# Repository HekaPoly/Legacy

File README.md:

# Legacy

Voici le _repository_ pour tous les fichiers du passé obscur de Métis. Amusez-vous à fouiller au travers ;)

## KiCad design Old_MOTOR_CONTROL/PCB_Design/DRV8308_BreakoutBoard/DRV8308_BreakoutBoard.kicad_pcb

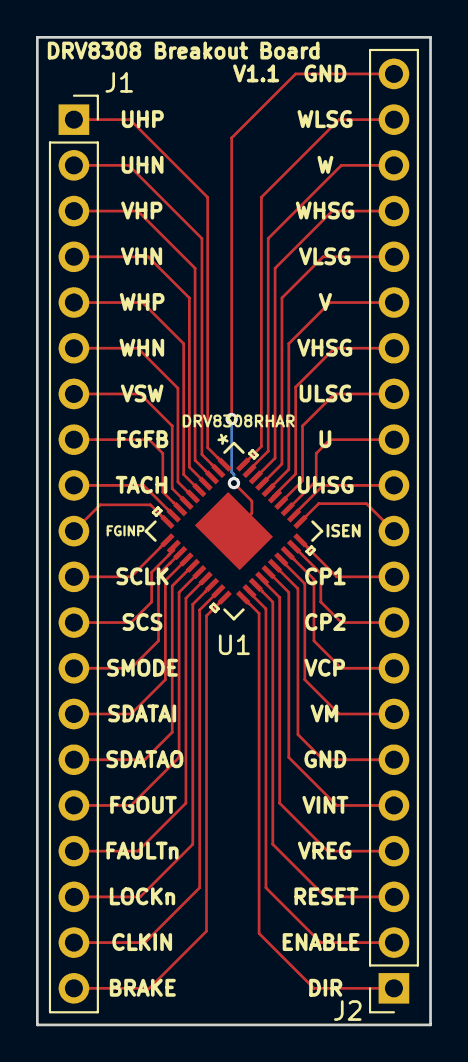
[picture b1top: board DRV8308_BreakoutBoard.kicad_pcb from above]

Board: 2 copper layers, 21.8 x 54.9 mm, 3 parts (0 on the bottom side), 41 nets.

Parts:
J1: Conn_01x20_Female; PinSocket_1x20_P2.54mm_Vertical
J2: Conn_01x21_Female; PinSocket_1x21_P2.54mm_Vertical
U1: DRV8308RHAR

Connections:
unnamed: J1.1, U1.1
unnamed: J1.2, U1.2
unnamed: J1.3, U1.3
unnamed: J1.4, U1.4
unnamed: J1.5, U1.5
unnamed: J1.6, U1.6
unnamed: J1.7, U1.7
unnamed: J1.8, U1.8
unnamed: J1.9, U1.9
unnamed: J1.10, U1.10
unnamed: J1.11, U1.11
unnamed: J1.12, U1.12
unnamed: J1.13, U1.13
unnamed: J1.14, U1.14
unnamed: J1.15, U1.15
unnamed: J1.16, U1.16
unnamed: J1.17, U1.17
unnamed: J1.18, U1.18
unnamed: J1.19, U1.19
unnamed: J1.20, U1.20
unnamed: J2.1, U1.21
unnamed: J2.2, U1.22
unnamed: J2.3, U1.23
unnamed: J2.4, U1.24
unnamed: J2.5, U1.25
unnamed: J2.6, U1.26
unnamed: J2.7, U1.27
unnamed: J2.8, U1.28
unnamed: J2.9, U1.29
unnamed: J2.10, U1.30
unnamed: J2.11, U1.31
unnamed: J2.12, U1.32
unnamed: J2.13, U1.33
unnamed: J2.14, U1.34
unnamed: J2.15, U1.35
unnamed: J2.16, U1.36
unnamed: J2.17, U1.37
unnamed: J2.18, U1.38
unnamed: J2.19, U1.39
unnamed: J2.20, U1.40
unnamed: J2.21, U1.41

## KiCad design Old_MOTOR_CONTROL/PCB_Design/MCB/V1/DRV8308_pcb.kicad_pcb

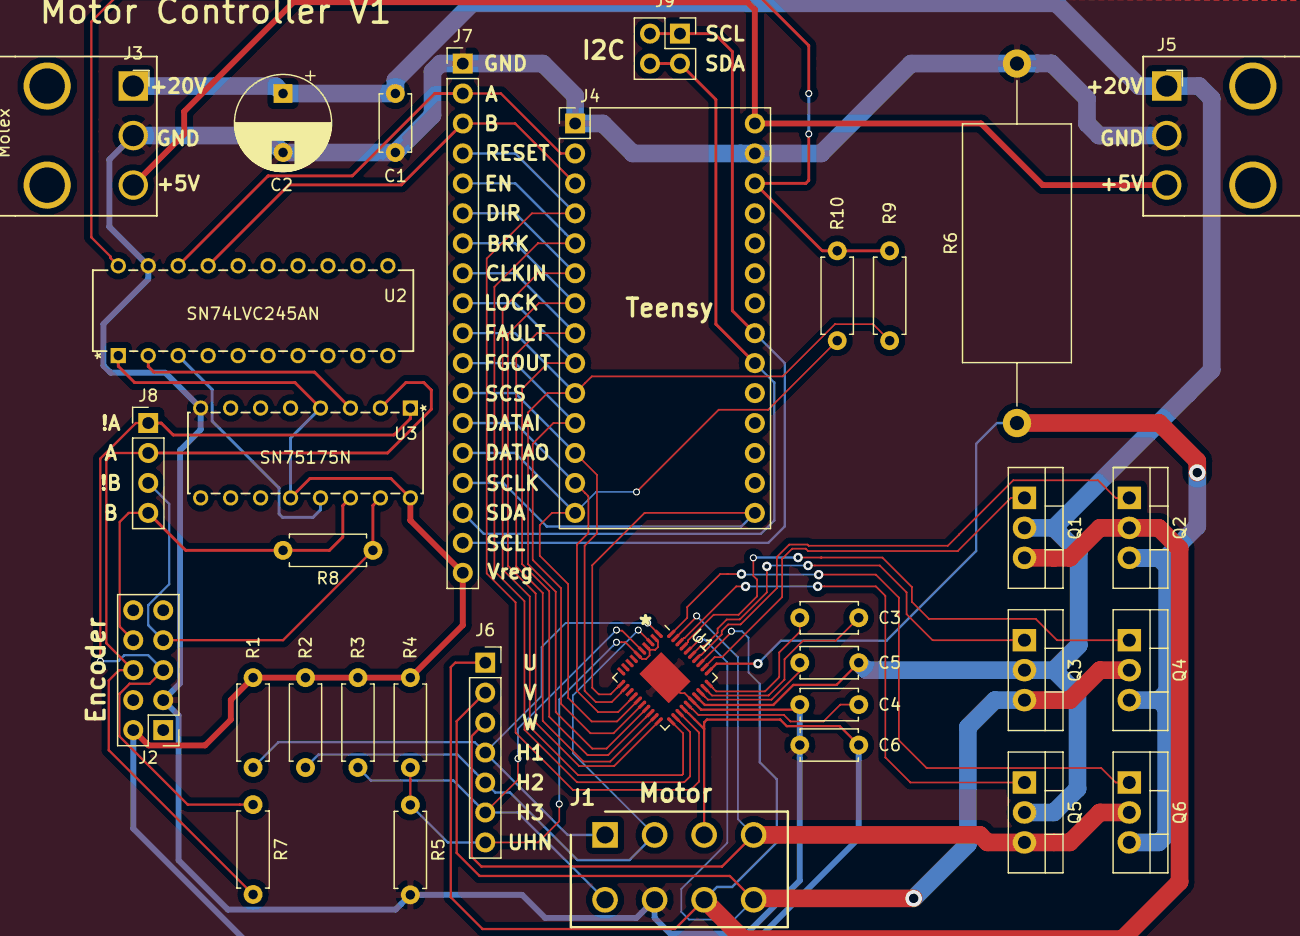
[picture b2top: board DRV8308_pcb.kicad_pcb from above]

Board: 2 copper layers, 34 parts (0 on the bottom side), 45 nets.

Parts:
C1, C3, C6: 0.1uF; C_Disc_D4.7mm_W2.5mm_P5.00mm
C2: 470uF; CP_Radial_D8.0mm_P5.00mm
C4, C5: 1uF; C_Disc_D4.7mm_W2.5mm_P5.00mm
J1: Molex_Motor; SHDR8W125P550X420_2X4_1800X960X1310P
J2: Conn_Encoder; PinHeader_2x05_P2.54mm_Vertical
J3: Molex_Pwr_In; Molex,1x3
J4: Teensy; TeensyLC
J5: Molex_Pwr_Out; Molex,1x3,Right
J6: Conn_01x07_Female; PinSocket_1x07_P2.54mm_Vertical
J7: PinsTeensy; PinHeader_1x18_P2.54mm_Vertical
J8: PinsEncoder; PinHeader_1x04_P2.54mm_Vertical
J9: Conn_I2C; PinSocket_2x02_P2.54mm_Vertical
Q1, Q2, Q3, Q4, Q5, Q6: Q_NMOS_IRLB8743; TO-220-3_Vertical
R1, R2, R3, R4, R5: 1K; R_Axial_DIN0207_L6.3mm_D2.5mm_P7.62mm_Horizontal
R6: 0.025; R_Axial_DIN0922_L20.0mm_D9.0mm_P30.48mm_Horizontal
R7, R8: 120; R_Axial_DIN0207_L6.3mm_D2.5mm_P7.62mm_Horizontal
R9, R10: 4.7k; R_Axial_DIN0207_L6.3mm_D2.5mm_P7.62mm_Horizontal
U1: DRV8308; Texas_S-PVQFN-N40_EP3.52x2.62mm
U2: SN74LVC245AN
U3: SN75175N

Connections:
/3.3V: J4.26, R9.2, R10.2, U2.20
/A: J4.2, J7.2, U2.18
/B: J4.3, J7.3, U2.17
/BRAKE: J4.7, J7.7, U1.20
/CLKIN: J4.8, J7.8, U1.19
/DATAI: J4.13, J7.13, U1.14
/DATAO: J4.14, J7.14, R10.1, U1.15
/DIR: J4.6, J7.6, U1.21
/ENABLE: J4.5, J7.5, U1.22
/ENC_!A: J2.5, J8.1, R7.1, U3.1
/ENC_!B: J2.7, J8.3, R8.1, U3.15
/ENC_A: J2.6, J8.2, R7.2, U3.2
/ENC_B: J2.8, J8.4, R8.2, U3.14
/FAULTn: J4.10, J7.10, R9.1, U1.17
/FGOUT: J4.11, J7.11, U1.16
/Hall_1: J1.1, J6.4, R1.2, U1.1
/Hall_2: J1.2, J6.5, R2.2, U1.3
/Hall_3: J1.5, J6.6, R3.2, U1.5
/LOCKn: J4.9, J7.9, U1.18
/Power/ISEN: Q2.3, Q4.3, Q6.3, R6.1, U1.31
/Power/UHSG: Q1.1, U1.32
/Power/ULSG: Q2.1, U1.34
/Power/VHSG: Q3.1, U1.35
/Power/VLSG: Q4.1, U1.37
/Power/WHSG: Q5.1, U1.38
/Power/WLSG: Q6.1, U1.40
/RESET: J4.4, J7.4, U1.23
/SCL: J4.21, J7.17, J9.1, J9.2
/SCLK: J4.15, J7.15, U1.11
/SCS: J4.12, J7.12, U1.12
/SDA: J4.20, J7.16, J9.3, J9.4
/UHN: J6.7, R4.2, R5.1, U1.2, U1.4, U1.6
/Vin: J3.3, J4.28, J5.3
/Vm: C1.1, C2.1, C5.1, J3.1, J5.1, Q1.2, Q3.2, Q5.2, U1.27
/Vreg: C6.2, J1.3, J2.2, J7.18, R1.1, R2.1, R3.1, R4.1, U1.24, U2.1, U3.4, U3.12, U3.16
GNDREF: C1.2, C2.2, C4.1, C6.1, J1.6, J2.3, J3.2, J4.1, J4.27, J5.2, J7.1, R5.2, R6.2, U1.26, U1.41, U2.19, U3.8
Motor_1: J1.7, J6.1, Q1.3, Q2.2, U1.33
Motor_2: J1.8, J6.2, Q3.3, Q4.2, U1.36
Motor_3: J1.4, J6.3, Q5.3, Q6.2, U1.39
unnamed: C3.1, U1.30
unnamed: C3.2, U1.29
unnamed: C4.2, U1.25
unnamed: C5.2, U1.28
unnamed: U2.2, U3.3
unnamed: U2.3, U3.13

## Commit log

2022-05-14 Transfer of old GUI repository
    Transfer of old GUI files contained in the GUI repository to the Legacy repository.
    These GUI files are not used anymore and have not been updated in 3 years. Deemed depricated.
2022-05-14 Transfer of Old_Acq folder from Elec repository
    Transfer of old acquisition files contained in the Old_Acq folder to the Legacy repository.
    These acquisition files are not used anymore and have not been updated in 3 years. Deemed depricated.

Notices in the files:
parts and their libraries:
Copyright 2016 Accelerated Designs. All rights reserved.
